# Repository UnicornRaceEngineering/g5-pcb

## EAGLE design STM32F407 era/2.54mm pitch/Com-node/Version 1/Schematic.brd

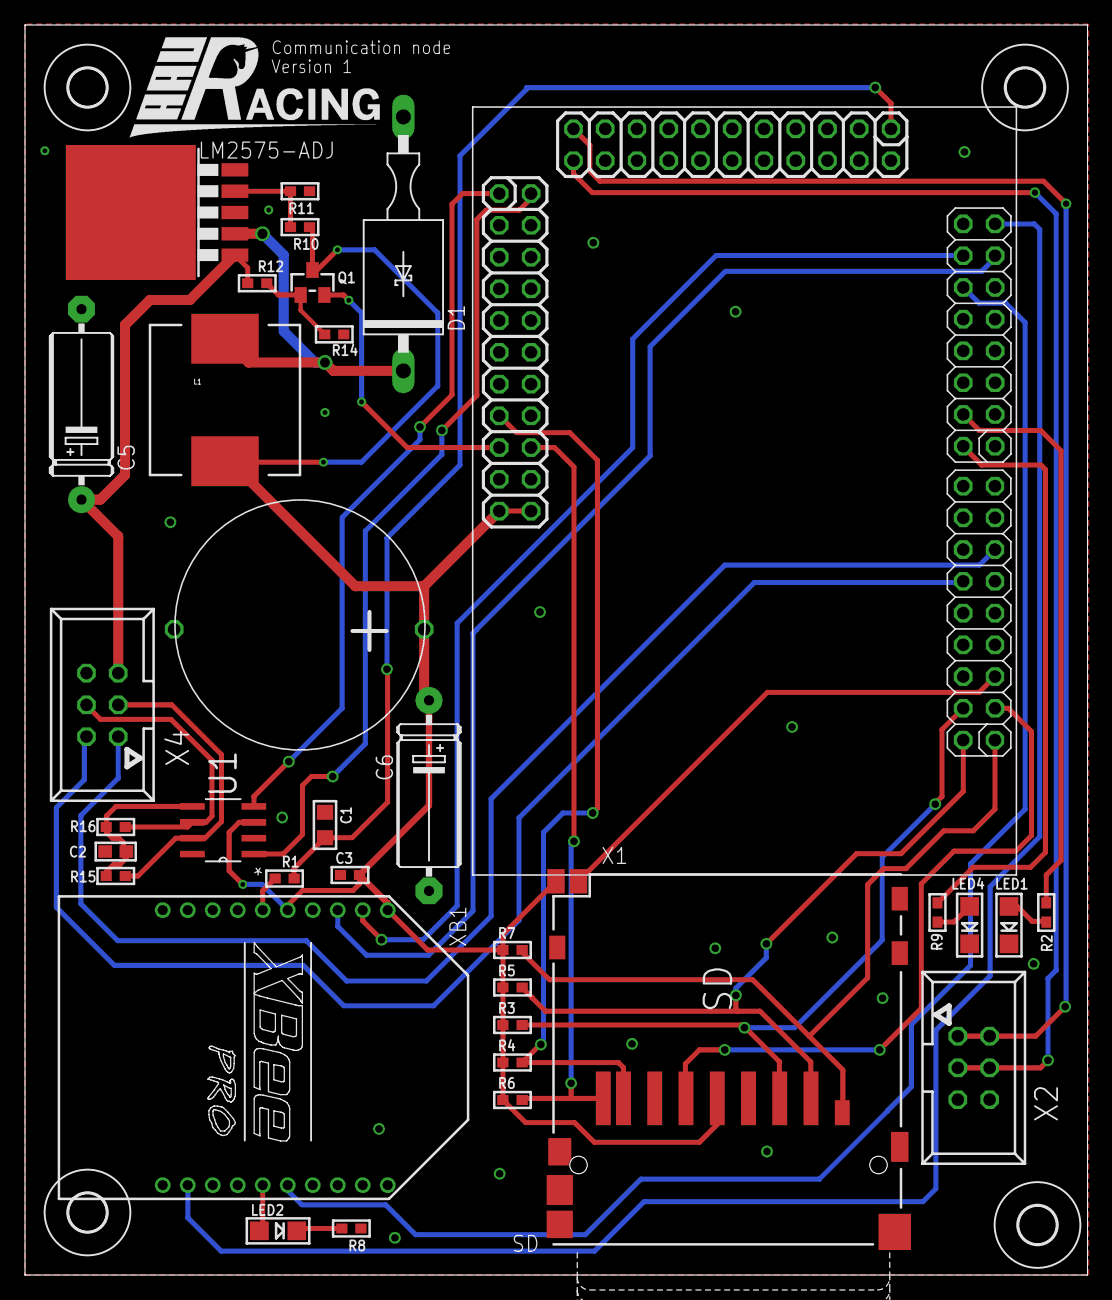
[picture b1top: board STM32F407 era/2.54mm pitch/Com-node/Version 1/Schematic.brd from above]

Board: 2 copper layers, 85.0 x 100.0 mm, 38 parts (0 on the bottom side), 35 nets.

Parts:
C1: 1µF; _0805
C2: 4n7; 0603
C3: 100nF; _0603
C5: 100uF; E15-5
C6: 220uF; E15-5
C8: SUPERCAP
D1: 1N5638; DO13M
H1, H2, H3, H4: MOUNT-HOLE3.0; 3,0
L1: 220µH; CDRH125
LED1, LED2, LED4: CHIPLED_1206
LM2575-ADJ: LM2596S; TO263-5
Q1: SOT23-WIDE
R1: 850; _0603
R2, R8, R9: 500; _0603
R3, R4, R5, R6, R7: 47k; _0603
R10: 1K69; _0603
R11: 1K; _0603
R12: 20K; _0603
R14: XXXXX; _0603
R15, R16: 60; _0603
U1: MAX13052ESA+; SOIC127P600X175-8N
U$1: CPU-BOARD; CPU-BOARD-JP1
X1: SDBMF; SDBMF-009XXBXX2
X2, X4: 057-006-1
XB1: XBEE-PRO

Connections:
+3V3: C3.2, C6.+, C8.P$1, L1.2, Q1.3, R3.1, R4.1, R5.1, R6.1, R7.1, R10.2, U1.3, U$1.P$43, U$1.P$44, X1.4, X1.SW3, XB1.1, XB1.5
+14V2: C5.+, LM2575-ADJ.1, R12.1, X4.5
CTS-XBEE: U$1.P$77, XB1.12
DEBUG-LED1: R9.2, U$1.P$64
DEBUG-LED2: R2.2, U$1.P$66
ECU_CAN_H: R15.2, U1.7, X4.3
ECU_CAN_L: R16.2, U1.6, X4.4
ECU_CAN_RX: U1.4, U$1.P$23
ECU_CAN_TX: U1.1, U$1.P$24
unnamed: R1.1, XB1.6
unnamed: LED1.A, R2.1
unnamed: LED2.A, XB1.15
unnamed: LED2.C, R8.2
unnamed: LED4.A, R9.1
unnamed: D1.C, L1.1, LM2575-ADJ.2
unnamed: LM2575-ADJ.4, R10.1, R11.2
unnamed: Q1.1, R12.2, R14.2
unnamed: C2.1, R15.1, R16.1, U1.5
PE: C1.1, C2.2, C3.1, C5.-, C6.-, C8.P$3, D1.A, LED1.C, LED4.C, LM2575-ADJ.3, LM2575-ADJ.5, R8.1, R11.1, R14.1, U1.2, U1.8, U$1.P$19, U$1.P$20, U$1.P$41, U$1.P$42, U$1.P$62, U$1.P$69, U$1.P$70, U$1.P$78, X1.3, X1.6, X2.5, X2.6, X4.6, XB1.10
RTS-XBEE: U$1.P$74, XB1.16
RX-XBEE: U$1.P$76, XB1.2
SDIO_CMD: R3.2, U$1.P$48, X1.2
SDIO_D0: R4.2, U$1.P$37, X1.7
SDIO_D1: R6.2, U$1.P$40, X1.8
SDIO_D2: R7.2, U$1.P$45, X1.9
SDIO_D3: R5.2, U$1.P$46, X1.1
SDIO_SCK: U$1.P$47, X1.5
SD_IN: U$1.P$49, X1.SW1
SS-XBEE: C1.2, R1.2, U$1.P$1
TX-XBEE: U$1.P$75, XB1.3
UART3_RX: U$1.P$22, X2.3, X2.4
UART3_TX: U$1.P$21, X2.1, X2.2
USART1_RX: U$1.P$57, X4.1
USART1_TX: U$1.P$56, X4.2
V-SENSE: Q1.2, U$1.P$39

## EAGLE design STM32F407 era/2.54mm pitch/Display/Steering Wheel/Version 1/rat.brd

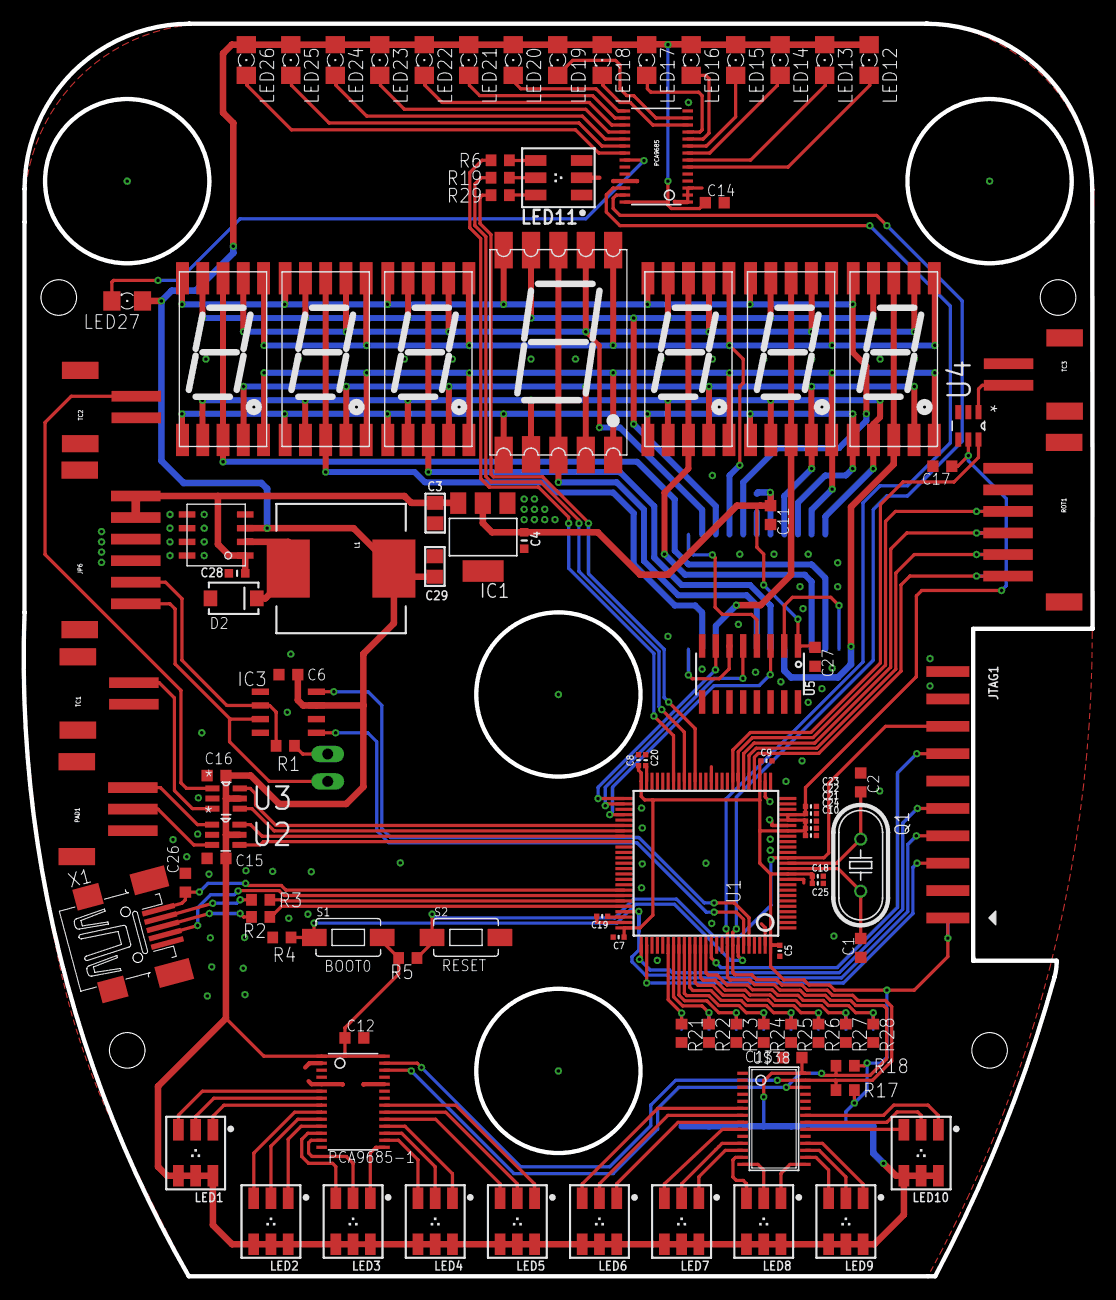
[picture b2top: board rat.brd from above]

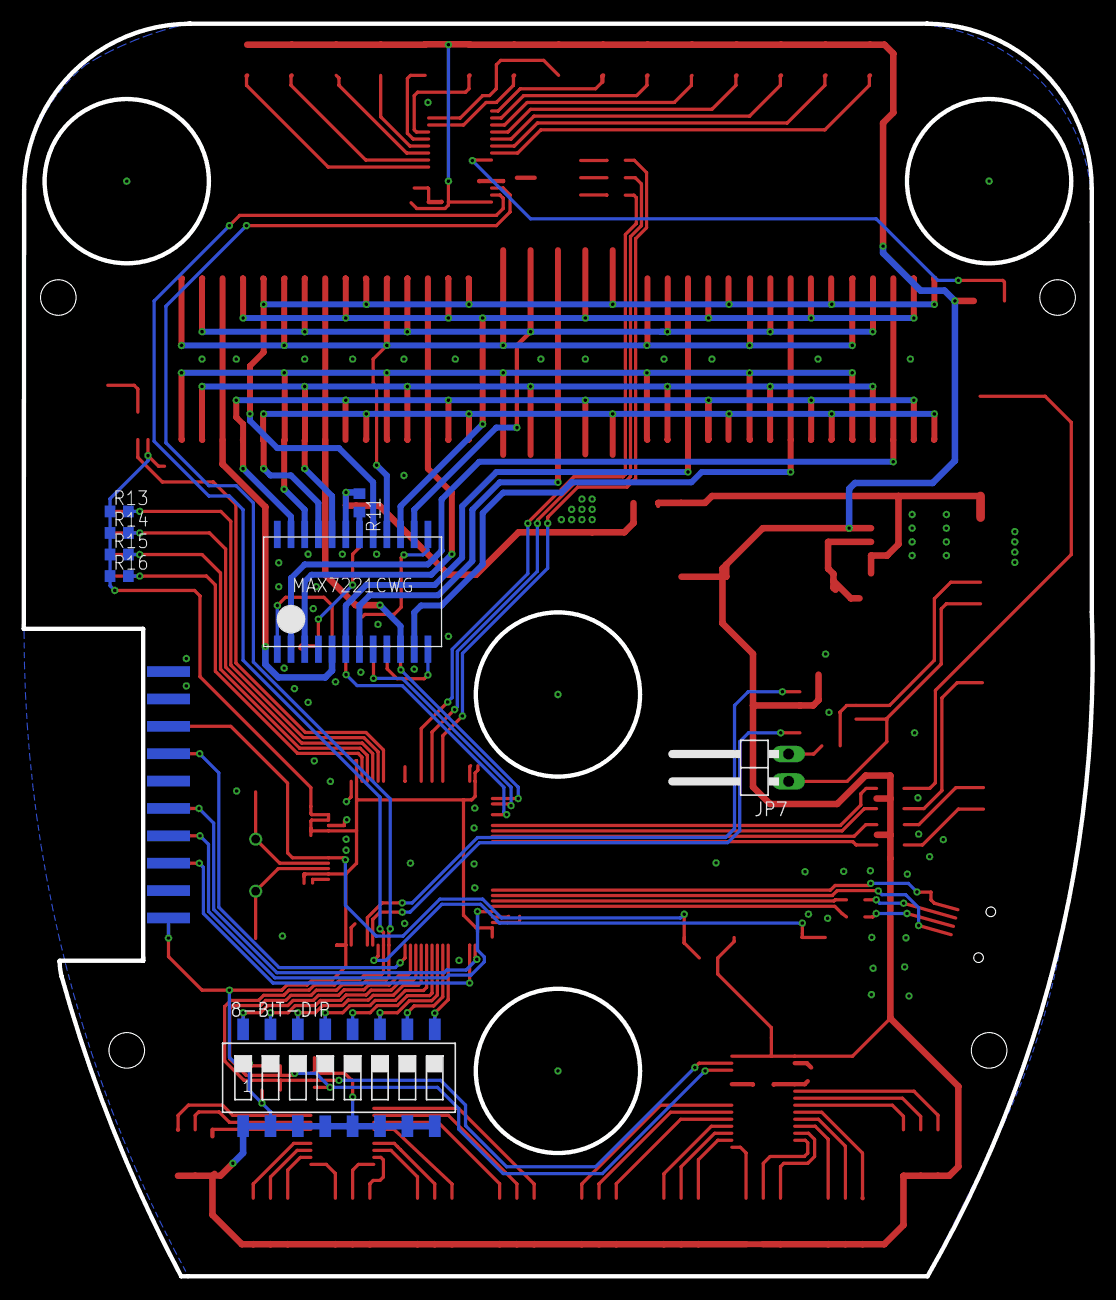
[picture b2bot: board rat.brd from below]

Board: 2 copper layers, 99.2 x 116.2 mm, 117 parts (8 on the bottom side), 124 nets.

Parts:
8-BIT-DIP: SWS008; SMS-008
C1, C2: 22pf; C0603K
C3, C29: 10u; 0805
C4: 22u; _0603MP
C5, C7, C8, C9, C10, C18, C21, C23: 100n; _0402MP
C6, C11, C12, C13, C14, C15, C16, C17, C27: 100nF; C0603K
C19, C20: 2u2; _0402MP
C22, C24: 1u; _0402MP
C25: 4u7; _0402MP
C26: 4u7; C0603K
C28: 100n; _0603MP
D2: B340A-13-F; SMA-DIODE
IC1: REG1117; SOT223
IC3: PCA82C250T; SO8
JP2, JP3, JP4, JP5: STAND-OFF
JP6: M06; S6B_PH
JP7: 1X02/90
JTAG1: JTAG-ARMEDGE; MOLEX20_RIGHTANGLE
L1: MSS1038-473MLC 47u; CDRH125
LED1, LED2, LED3, LED4, LED5, LED6, LED7, LED8, LED9, LED10, LED11: RGBLED_PLCC6
LED12, LED13, LED14, LED15, LED16: BLUE; 1206
LED17, LED18, LED19, LED20, LED21: RED; 1206
LED22, LED23, LED24, LED25, LED26, LED27: GREEN; 1206
MAX7221: MAX7221-SMD; MAX7221
PAD1: S3B-PH
PCA9685, PCA9685-1: TSSOP28
Q1: 25 MHz; HC49U70
R1: 120; R0603
R2, R3: 22; R0603
R4, R5: 500; R0603
R6, R19, R29: 220; R0603
R11: 9.5k; R0603
R13, R14, R15, R16, R17, R18: 10k; R0603
R21, R22, R23, R24, R25, R26, R27, R28: 200; R0603
ROT1: M06; S6B_PH
S1, S2: TACTILE-SWITCH-1101NE
TC1: NEUT; S2B-PH
TC2: LC; S2B-PH
TC3: tc; S2B-PH
U1: SQFP-S-14X14-100
U2, U3, U4: MAX6817EUT+T; SOT95P280X145-6N
U5: SOIC16
U$2, U$3, U$4, U$6, U$7, U$8: REDSEVENSEGMENT; REDSEGMENT
U$5: BIGSEVENSEGMENT
U$10: AP1509; SOP-8L
U$38: TLC59116; TSSOP28
X1: 32005-201

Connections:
3.3V: 8-BIT-DIP.1, 8-BIT-DIP.2, 8-BIT-DIP.3, 8-BIT-DIP.4, 8-BIT-DIP.5, 8-BIT-DIP.6, 8-BIT-DIP.7, 8-BIT-DIP.8, C5.1, C6.1, C7.1, C8.1, C9.1, C10.1, C12.1, C13.1, C14.1, C15.1, C16.1, C17.1, C18.1, C21.1, C22.1, C23.1, C24.1, C25.1, C29.1, IC3.3, JTAG1.1, JTAG1.2, L1.1, LED1.4, LED1.5, LED1.6, LED2.4, LED2.5, LED2.6, LED3.4, LED3.5, LED3.6, LED4.4, LED4.5, LED4.6, LED5.4, LED5.5, LED5.6, LED6.4, LED6.5, LED6.6, LED7.4, LED7.5, LED7.6, LED8.4, LED8.5, LED8.6, LED9.4, LED9.5, LED9.6, LED10.4, LED10.5, LED10.6, LED12.A, LED13.A, LED14.A, LED15.A, LED16.A, LED17.A, LED18.A, LED19.A, LED20.A, LED21.A, LED22.A, LED23.A, LED24.A, LED25.A, LED26.A, LED27.A, PCA9685.28, PCA9685-1.1, PCA9685-1.28, R5.2, R13.1, R14.1, R15.1, R16.1, R17.2, R18.2, S1.P$2, U1.11, U1.19, U1.21, U1.22, U1.28, U1.50, U1.75, U1.100, U2.5, U3.5, U4.5, U$10.P$3, U$38.28
5.0V: C4.1, C11.1, C27.1, IC1.2, MAX7221.VCC, R11.1, U5.1
12V: C3.2, C28.2, IC1.3, JP6.5, JP6.6, U$10.P$1
CANJUMP1: IC3.7, JP6.1, JP7.1
CANJUMP2: JP7.2, R1.2
CAN_RX: IC3.1, U1.95
CAN_TX: IC3.4, U1.96
DIP1: 8-BIT-DIP.9, R21.1, U1.81
DIP2: 8-BIT-DIP.10, R22.1, U1.82
DIP3: 8-BIT-DIP.11, R23.1, U1.83
DIP4: 8-BIT-DIP.12, R24.1, U1.84
DIP5: 8-BIT-DIP.13, R25.1, U1.85
DIP6: 8-BIT-DIP.14, R26.1, U1.86
DIP7: 8-BIT-DIP.15, R27.1, U1.87
DIP8: 8-BIT-DIP.16, R28.1, U1.88
GND: C1.1, C2.1, C3.1, C4.2, C5.2, C6.2, C7.2, C8.2, C9.2, C10.2, C11.2, C12.2, C13.2, C14.2, C15.2, C16.2, C17.2, C18.2, C19.2, C20.2, C21.2, C22.2, C23.2, C24.2, C25.2, C26.2, C27.2, C28.1, C29.2, D2.A, IC1.1, IC3.2, IC3.8, JP6.3, JP6.4, JTAG1.3, JTAG1.4, JTAG1.6, JTAG1.8, JTAG1.10, JTAG1.12, JTAG1.14, JTAG1.16, JTAG1.18, JTAG1.20, LED11.1, LED11.2, LED11.3, MAX7221.GND, MAX7221.GND1, PAD1.1, PCA9685.1, PCA9685.2, PCA9685.3, PCA9685.4, PCA9685.5, PCA9685.14, PCA9685.23, PCA9685.24, PCA9685.25, PCA9685-1.2, PCA9685-1.3, PCA9685-1.4, PCA9685-1.5, PCA9685-1.14, PCA9685-1.23, PCA9685-1.24, PCA9685-1.25, R4.1, R21.2, R22.2, R23.2, R24.2, R25.2, R26.2, R27.2, R28.2, ROT1.1, ROT1.2, S2.P$2, TC1.1, TC2.1, TC3.1, U1.10, U1.20, U1.27, U1.37, U1.74, U1.99, U2.2, U3.2, U4.2, U5.8, U$10.P$4, U$10.P$5, U$10.P$6, U$10.P$7, U$10.P$8, U$38.10, U$38.19, U$38.24, X1.5, X1.M1, X1.M2, X1.M3, X1.M4
JTAG-TCK: JTAG1.9, U1.76
JTAG-TDI: JTAG1.5, U1.77
JTAG-TDO: JTAG1.13, U1.89
JTAG-TMS: JTAG1.7, U1.72
LC: U1.56, U3.6
unnamed: C2.2, Q1.1, U1.13
unnamed: C1.2, Q1.2, U1.12
unnamed: MAX7221.SEG_A, U$2.A, U$3.A, U$4.A, U$5.A, U$6.A, U$7.A, U$8.A
unnamed: MAX7221.CLK, U5.4
unnamed: MAX7221.LOAD, U5.6
unnamed: MAX7221.SEG_B, U$2.B, U$3.B, U$4.B, U$5.B, U$6.B, U$7.B, U$8.B
unnamed: MAX7221.DIN, U5.2
unnamed: MAX7221.SEG_C, U$2.C, U$3.C, U$4.C, U$5.C, U$6.C, U$7.C, U$8.C
unnamed: LED13.C, PCA9685.7
unnamed: C19.1, U1.73
unnamed: LED14.C, PCA9685.8
unnamed: MAX7221.SEG_D, U$2.D, U$3.D, U$4.D, U$5.D, U$6.D, U$7.D, U$8.D
unnamed: MAX7221.SEG_E, U$2.E, U$3.E, U$4.E, U$5.E, U$6.E, U$7.E, U$8.E
unnamed: MAX7221.SEG_F, U$2.F, U$3.F, U$4.F, U$5.F, U$6.F, U$7.F, U$8.F
unnamed: MAX7221.SEG_G, U$2.G, U$3.G, U$4.G, U$5.G, U$6.G, U$7.G, U$8.G
unnamed: MAX7221.DIG0, U$2.GND, U$2.GND2
unnamed: MAX7221.DIG1, U$3.GND, U$3.GND2
unnamed: MAX7221.DIG2, U$4.GND, U$4.GND2
unnamed: MAX7221.DIG3, U$5.GND, U$5.GND2
unnamed: MAX7221.DIG4, U$6.GND, U$6.GND2
unnamed: MAX7221.DIG5, U$7.GND, U$7.GND2
unnamed: MAX7221.DIG6, U$8.GND, U$8.GND2
unnamed: LED15.C, PCA9685.9
unnamed: C20.1, U1.49
unnamed: MAX7221.SEG_DP, U$2.DP, U$3.DP, U$4.DP, U$5.DOT, U$6.DP, U$7.DP, U$8.DP
unnamed: R2.2, X1.3
unnamed: MAX7221.ISET, R11.2
unnamed: R3.2, X1.2
unnamed: LED11.5, R19.1
unnamed: R4.2, S1.P$1, U1.94
unnamed: LED11.6, R29.1
unnamed: LED11.4, R6.1
unnamed: LED16.C, PCA9685.10
unnamed: LED17.C, PCA9685.11
unnamed: LED18.C, PCA9685.12
unnamed: LED19.C, PCA9685.13
unnamed: LED20.C, PCA9685.15
unnamed: LED21.C, PCA9685.16
unnamed: LED22.C, PCA9685.17
unnamed: LED23.C, PCA9685.18
unnamed: LED24.C, PCA9685.19
unnamed: LED25.C, PCA9685.20
unnamed: LED26.C, PCA9685.21
unnamed: LED1.3, PCA9685-1.6
unnamed: D2.C, L1.2, U$10.P$2
unnamed: LED1.2, PCA9685-1.7
unnamed: LED1.1, PCA9685-1.8
unnamed: LED2.3, PCA9685-1.9
unnamed: IC3.6, JP6.2, R1.1
unnamed: LED2.2, PCA9685-1.10
unnamed: LED2.1, PCA9685-1.11
unnamed: LED3.3, PCA9685-1.12
unnamed: LED3.2, PCA9685-1.13
unnamed: LED3.1, PCA9685-1.15
unnamed: LED4.3, PCA9685-1.16
unnamed: LED12.C, PCA9685.6
unnamed: LED4.2, PCA9685-1.17
unnamed: LED4.1, PCA9685-1.18
unnamed: LED5.3, PCA9685-1.19
unnamed: LED5.2, PCA9685-1.20
unnamed: LED5.1, PCA9685-1.21
unnamed: LED6.3, U$38.6
unnamed: LED6.2, U$38.7
unnamed: LED6.1, U$38.8
unnamed: LED7.3, U$38.9
unnamed: LED7.2, U$38.11
unnamed: LED7.1, U$38.12
unnamed: LED8.3, U$38.13
unnamed: LED8.2, U$38.14
unnamed: LED8.1, U$38.15
unnamed: LED9.3, U$38.16
unnamed: LED9.2, U$38.17
unnamed: LED9.1, U$38.18
unnamed: LED10.3, U$38.20
unnamed: LED10.2, U$38.21
unnamed: LED10.1, U$38.22
unnamed: LED27.C, PCA9685.22
unnamed: TC1.2, U3.3
unnamed: PAD1.3, U2.1
unnamed: PAD1.2, U2.3
unnamed: TC2.2, U3.1
unnamed: TC3.2, U4.1
NEUT: U1.57, U3.4
PADDOWN: U1.59, U2.4
PADUP: U1.58, U2.6
RESET: JTAG1.15, R5.1, S2.P$1, U1.14
ROTSW1: R16.2, ROT1.6, U1.29
ROTSW2: R15.2, ROT1.5, U1.30
ROTSW3: R14.2, ROT1.4, U1.31
ROTSW4: R13.2, ROT1.3, U1.32
SCL: PCA9685.26, PCA9685-1.26, R18.1, U1.92, U$38.26
SDA: PCA9685.27, PCA9685-1.27, R17.1, U1.93, U$38.27
SLBLUE: R29.2, U1.40
SLGREEN: R19.2, U1.42
SLRED: R6.2, U1.44
SPI-LOAD: U1.51, U5.7
SPI-MOSI: U1.54, U5.3
SPI-SCK: U1.52, U5.5
TCTEMPOFF: U1.33, U4.6
USB_DM: R3.1, U1.70
USB_DP: R2.1, U1.71
USB_ID: U1.69, X1.4
USB_VBUS: C26.1, U1.68, X1.1

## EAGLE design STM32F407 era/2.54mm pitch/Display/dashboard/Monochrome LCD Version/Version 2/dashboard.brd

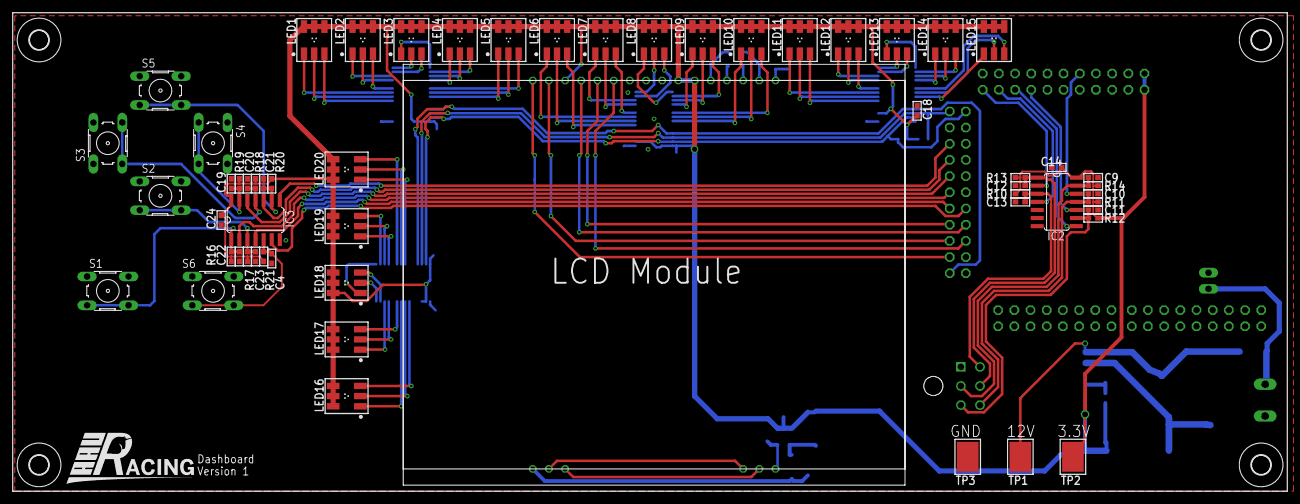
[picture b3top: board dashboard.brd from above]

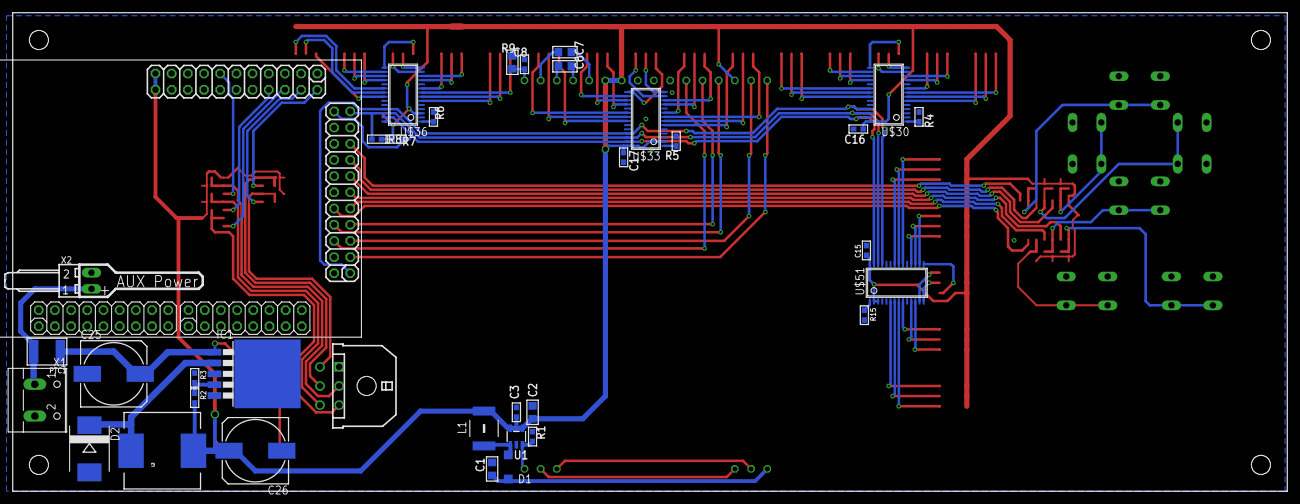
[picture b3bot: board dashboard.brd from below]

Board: 2 copper layers, 200.0 x 75.1 mm, 97 parts (36 on the bottom side), 110 nets.

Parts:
C1: 220n; _0805
C2: 1u; _0805
C3, C4, C8, C9, C10, C11, C12, C13, C14, C15, C16, C17, C18, C19, C20, C21, C22, C23, C24: 100n; _0603
C6, C7: 2u; _0805
C25: 470u; 153CLV-1012
C26: 220u; 153CLV-1012
D1: MBR0520LT; SOD123
D2: SMC
H1, H2, H3, H4: MOUNT-HOLE3.0; 3,0
IC1: TO263-5
IC2, IC3: 74HC14D; SO14
L1: WE-PD4S; S
L2: MSS1583-683MED; CDRH125
LED1, LED2, LED3, LED4, LED5, LED6, LED7, LED8, LED9, LED10, LED11, LED12, LED13, LED14, LED15, LED16, LED17, LED18, LED19, LED20: RGBLED_PLCC6
PTC1: PTC1812
R1: 15; _0603
R2: 1k69; _0603
R3: 1k; _0603
R4, R5, R6, R15: 931; _0603
R7, R8, R10, R11, R12, R13, R14, R16, R17, R18, R19, R20, R21: 500; _0603
R9: 10m; _0805
S1, S2, S3, S4, S5, S6: B3F-10XX
TP1, TP2, TP3: TESTPOINT_SMT
U1: CAT4238TD-GT3; SOT23-5
U$1: CPU-BOARD; CPU-BOARD-JP1
U$10: EA-DOGXL160W-7
U$30, U$33, U$36, U$51: TLC59116; TSSOP28
U$42: MICROFIT6; 43045-0600
X1: W237-102
X2: 22-05-7028-02; 7395-02

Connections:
3.3V: C2.1, C3.1, C14.1, C15.1, C16.1, C17.1, C18.1, C24.1, C26.+, IC2.14, IC3.14, L1.2, L2.2, LED1.4, LED1.5, LED1.6, LED2.4, LED2.5, LED2.6, LED3.4, LED3.5, LED3.6, LED4.4, LED4.5, LED4.6, LED5.4, LED5.5, LED5.6, LED6.4, LED6.5, LED6.6, LED7.4, LED7.5, LED7.6, LED8.4, LED8.5, LED8.6, LED9.4, LED9.5, LED9.6, LED10.4, LED10.5, LED10.6, LED11.4, LED11.5, LED11.6, LED12.4, LED12.5, LED12.6, LED13.4, LED13.5, LED13.6, LED14.4, LED14.5, LED14.6, LED15.4, LED15.5, LED15.6, LED16.4, LED16.5, LED16.6, LED17.4, LED17.5, LED17.6, LED18.4, LED18.5, LED18.6, LED19.4, LED19.5, LED19.6, LED20.4, LED20.5, LED20.6, R2.2, R7.2, R8.2, R10.2, R11.2, R12.2, R13.2, R14.2, R16.2, R17.2, R18.2, R19.2, R20.2, R21.2, TP2.P$1, U1.4, U1.5, U$1.P$43, U$1.P$44, U$10.P$22, U$10.P$23, U$10.P$30, U$30.28, U$33.2, U$33.28, U$36.3, U$36.28, U$51.2, U$51.3, U$51.28
12V: PTC1.P$2, X1.1, X2.1
BTN1: C12.2, IC2.1, R13.1, U$42.P$5
BTN1S: IC2.2, U$1.P$24
BTN2: C13.2, IC2.3, R10.1, U$42.P$4
BTN2S: IC2.4, U$1.P$26
BTN3: C10.2, IC2.11, R11.1, U$42.P$6
BTN3S: IC2.10, U$1.P$30
BTN4: C9.2, IC2.13, R14.1, U$42.P$2
BTN4S: IC2.12, U$1.P$35
BTN5: C11.2, IC2.9, R12.1, U$42.P$3
BTN5S: IC2.8, U$1.P$28
CD: U$1.P$6, U$10.P$27
GND: C1.2, C2.2, C3.2, C4.1, C8.1, C9.1, C10.1, C11.1, C12.1, C13.1, C14.2, C15.2, C16.2, C17.2, C18.2, C19.1, C20.1, C21.1, C22.1, C23.1, C24.2, C25.-, C26.-, D2.A, IC1.3, IC1.5, IC1.6, IC2.5, IC2.7, IC3.7, R1.2, R3.1, R4.2, R5.2, R6.2, R9.1, R15.2, S1.1, S1.2, S2.1, S2.2, S3.1, S3.2, S4.1, S4.2, S5.1, S5.2, S6.1, S6.2, TP3.P$1, U1.2, U$1.P$19, U$1.P$20, U$1.P$41, U$1.P$42, U$1.P$62, U$1.P$69, U$1.P$70, U$1.P$78, U$10.P$24, U$10.P$25, U$10.P$26, U$30.2, U$30.3, U$30.4, U$30.5, U$30.10, U$30.19, U$30.24, U$33.3, U$33.4, U$33.5, U$33.10, U$33.19, U$33.24, U$36.2, U$36.4, U$36.5, U$36.10, U$36.19, U$36.24, U$42.P$1, U$51.4, U$51.5, U$51.10, U$51.19, U$51.24, X1.2, X2.2
LCD_CLOCK: U$1.P$3, U$10.P$32
LCD_CS: U$1.P$7, U$10.P$28
LCD_DATA: U$1.P$5, U$10.P$31
LCD_RESET: U$1.P$8, U$10.P$29
unnamed: U$10.P$2, U$10.P$14
unnamed: U$10.P$3, U$10.P$15
unnamed: R1.1, U1.3, U$10.P$16
unnamed: C1.1, D1.C, U$10.P$1
unnamed: D1.A, L1.1, U1.1
unnamed: D2.C, IC1.2, L2.1
unnamed: LED1.3, U$30.6
unnamed: LED1.2, U$30.7
unnamed: IC1.4, R2.1, R3.2
unnamed: LED1.1, U$30.8
unnamed: LED2.3, U$30.9
unnamed: LED2.2, U$30.11
unnamed: LED2.1, U$30.12
unnamed: LED3.3, U$30.13
unnamed: LED3.2, U$30.14
unnamed: LED3.1, U$30.15
unnamed: LED4.3, U$30.16
unnamed: LED4.2, U$30.17
unnamed: LED4.1, U$30.18
unnamed: LED5.3, U$30.20
unnamed: LED5.2, U$30.21
unnamed: LED5.1, U$30.22
unnamed: LED6.3, U$33.6
unnamed: LED6.2, U$33.7
unnamed: LED6.1, U$33.8
unnamed: LED7.3, U$33.9
unnamed: LED7.2, U$33.11
unnamed: LED7.1, U$33.12
unnamed: LED8.3, U$33.13
unnamed: LED8.2, U$33.14
unnamed: LED8.1, U$33.15
unnamed: LED9.3, U$33.16
unnamed: LED9.2, U$33.17
unnamed: LED9.1, U$33.18
unnamed: LED10.3, U$33.20
unnamed: LED10.2, U$33.21
unnamed: LED10.1, U$33.22
unnamed: LED11.3, U$36.6
unnamed: LED11.2, U$36.7
unnamed: LED11.1, U$36.8
unnamed: LED12.3, U$36.9
unnamed: LED12.2, U$36.11
unnamed: LED12.1, U$36.12
unnamed: LED13.3, U$36.13
unnamed: LED13.2, U$36.14
unnamed: LED13.1, U$36.15
unnamed: LED14.3, U$36.16
unnamed: LED14.2, U$36.17
unnamed: LED14.1, U$36.18
unnamed: LED15.3, U$36.20
unnamed: LED15.2, U$36.21
unnamed: LED15.1, U$36.22
unnamed: R4.1, U$30.1
unnamed: LED16.3, U$51.6
unnamed: R5.1, U$33.1
unnamed: R6.1, U$36.1
unnamed: C6.1, U$10.P$20
unnamed: C7.1, U$10.P$21
unnamed: C6.2, U$10.P$19
unnamed: C7.2, U$10.P$18
unnamed: C8.2, R9.2, U$10.P$17
unnamed: LED16.2, U$51.7
unnamed: LED16.1, U$51.8
unnamed: LED17.3, U$51.9
unnamed: LED17.2, U$51.11
unnamed: LED17.1, U$51.12
unnamed: LED18.3, U$51.13
unnamed: LED18.2, U$51.14
unnamed: LED18.1, U$51.15
unnamed: LED19.3, U$51.16
unnamed: LED19.2, U$51.17
unnamed: LED19.1, U$51.18
unnamed: LED20.3, U$51.20
unnamed: LED20.2, U$51.21
unnamed: LED20.1, U$51.22
unnamed: R15.1, U$51.1
SCL: R8.1, U$1.P$21, U$30.26, U$33.26, U$36.26, U$51.26
SDA: R7.1, U$1.P$22, U$30.27, U$33.27, U$36.27, U$51.27
SW1: C22.2, IC3.1, R16.1, S1.3, S1.4
SW1S: IC3.2, U$1.P$11
SW2: C23.2, IC3.3, R17.1, S2.3, S2.4
SW2S: IC3.4, U$1.P$9
SW3: C20.2, IC3.11, R18.1, S3.3, S3.4
SW3S: IC3.10, U$1.P$15
SW4: C19.2, IC3.13, R19.1, S4.3, S4.4
SW4S: IC3.12, U$1.P$13
SW5: C21.2, IC3.9, R20.1, S5.3, S5.4
SW5S: IC3.8, U$1.P$17
SW6: C4.2, IC3.5, R21.1, S6.3, S6.4
SW6S: IC3.6, U$1.P$10
VSUP: C25.+, IC1.1, PTC1.P$1, TP1.P$1
~RESET: U$1.P$1, U$30.25, U$33.25, U$36.25, U$51.25

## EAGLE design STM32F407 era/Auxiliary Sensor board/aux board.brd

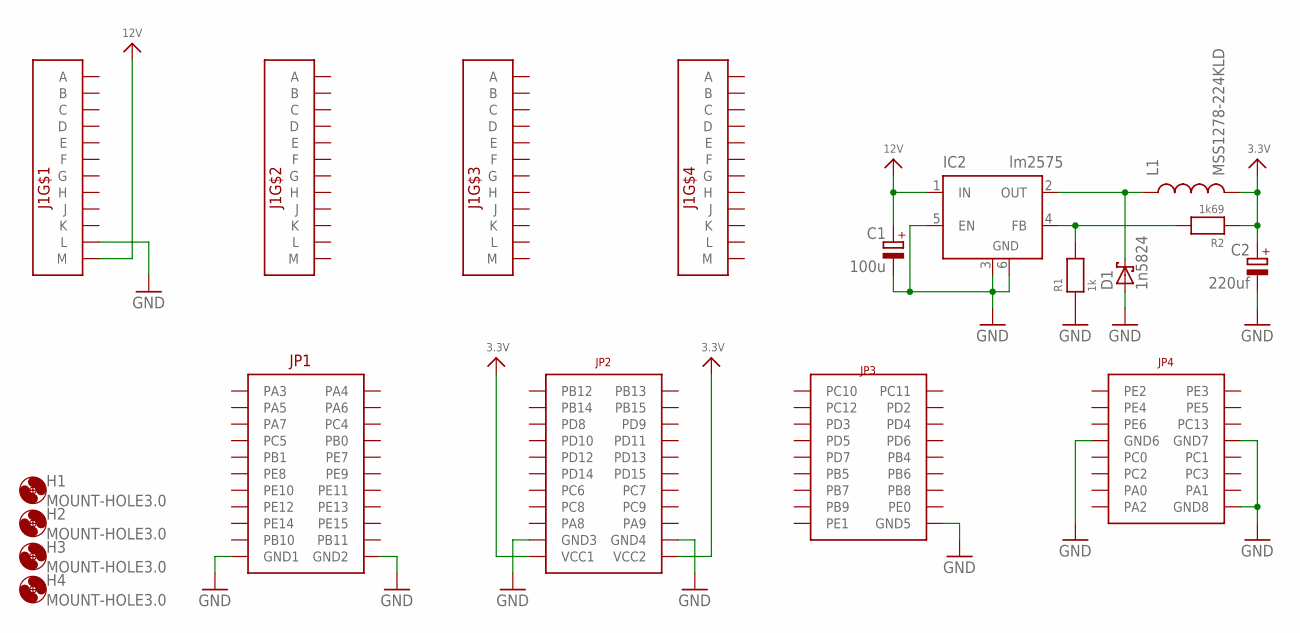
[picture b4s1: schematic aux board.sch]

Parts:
C1: 100u; E2,5-7
C2: 220uf; E3,5-8
D1: 1n5824; F126Z12
H1, H2, H3, H4: MOUNT-HOLE3.0; 3,0
IC2: lm2575; TO263-5
J1: AUTOCONNECTOR
L1: MSS1278-224KLD; CDRH125
R1: 1k; _0603
R2: 1k69; _0603
U$1: CPU-BOARD; CPU-BOARD-JP1

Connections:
3.3V: C2.+, L1.2, R2.1, U$1.P$43 (VCC1), U$1.P$44 (VCC2)
12V: C1.+, IC2.1 (IN), J1.M1 (M)
GND: C1.-, C2.-, D1.A, IC2.3 (GND), IC2.5 (EN), IC2.6 (GND), J1.L1 (L), R1.1, U$1.P$21 (GND1), U$1.P$22 (GND2), U$1.P$41 (GND3), U$1.P$42 (GND4), U$1.P$62 (GND5), U$1.P$69 (GND6), U$1.P$70 (GND7), U$1.P$78 (GND8)
unnamed: IC2.4 (FB), R1.2, R2.2
unnamed: D1.C, IC2.2 (OUT), L1.1

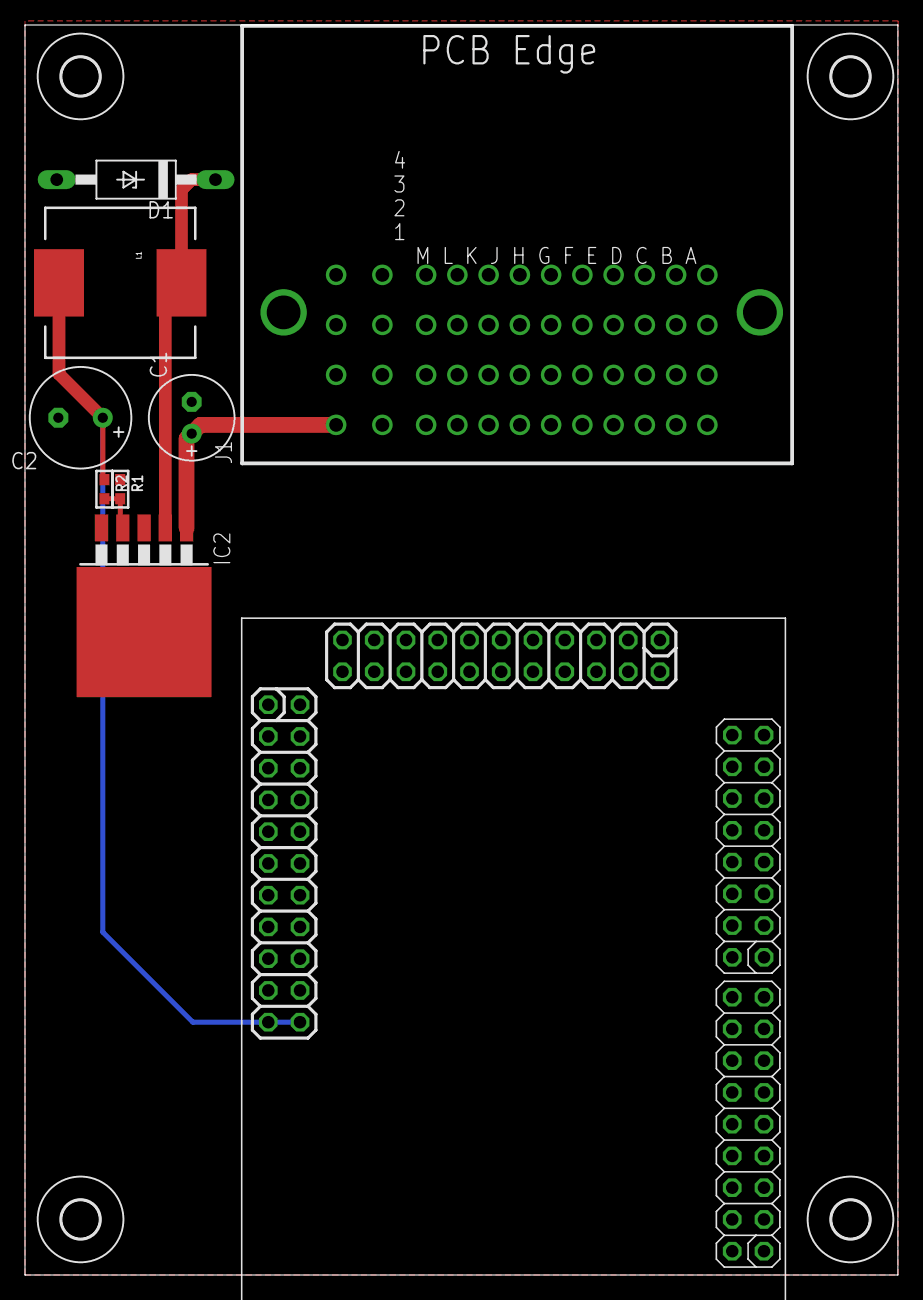
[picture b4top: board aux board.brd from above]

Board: 2 copper layers, 69.8 x 100.0 mm, 13 parts (0 on the bottom side), 5 nets.

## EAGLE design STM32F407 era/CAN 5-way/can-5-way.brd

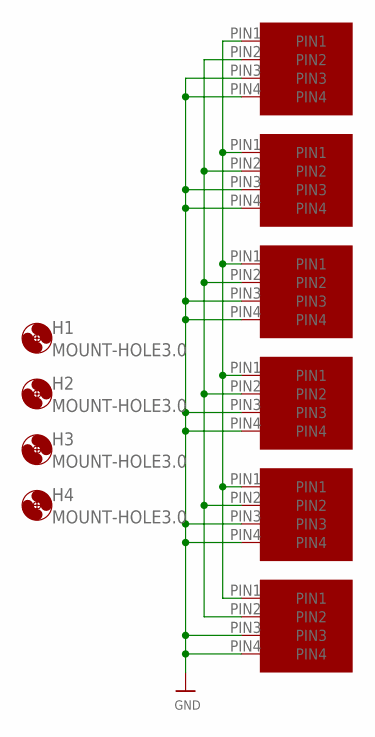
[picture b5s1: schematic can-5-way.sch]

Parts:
H1, H2, H3, H4: MOUNT-HOLE3.0; 3,0
U$1, U$2, U$3, U$4, U$5, U$7: MICROFIT4; MICROFIT4SOCK

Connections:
GND: U$1.PIN3, U$1.PIN4, U$2.PIN3, U$2.PIN4, U$3.PIN3, U$3.PIN4, U$4.PIN3, U$4.PIN4, U$5.PIN3, U$5.PIN4, U$7.PIN3, U$7.PIN4
unnamed: U$1.PIN1, U$2.PIN1, U$3.PIN1, U$4.PIN1, U$5.PIN1, U$7.PIN1
unnamed: U$1.PIN2, U$2.PIN2, U$3.PIN2, U$4.PIN2, U$5.PIN2, U$7.PIN2

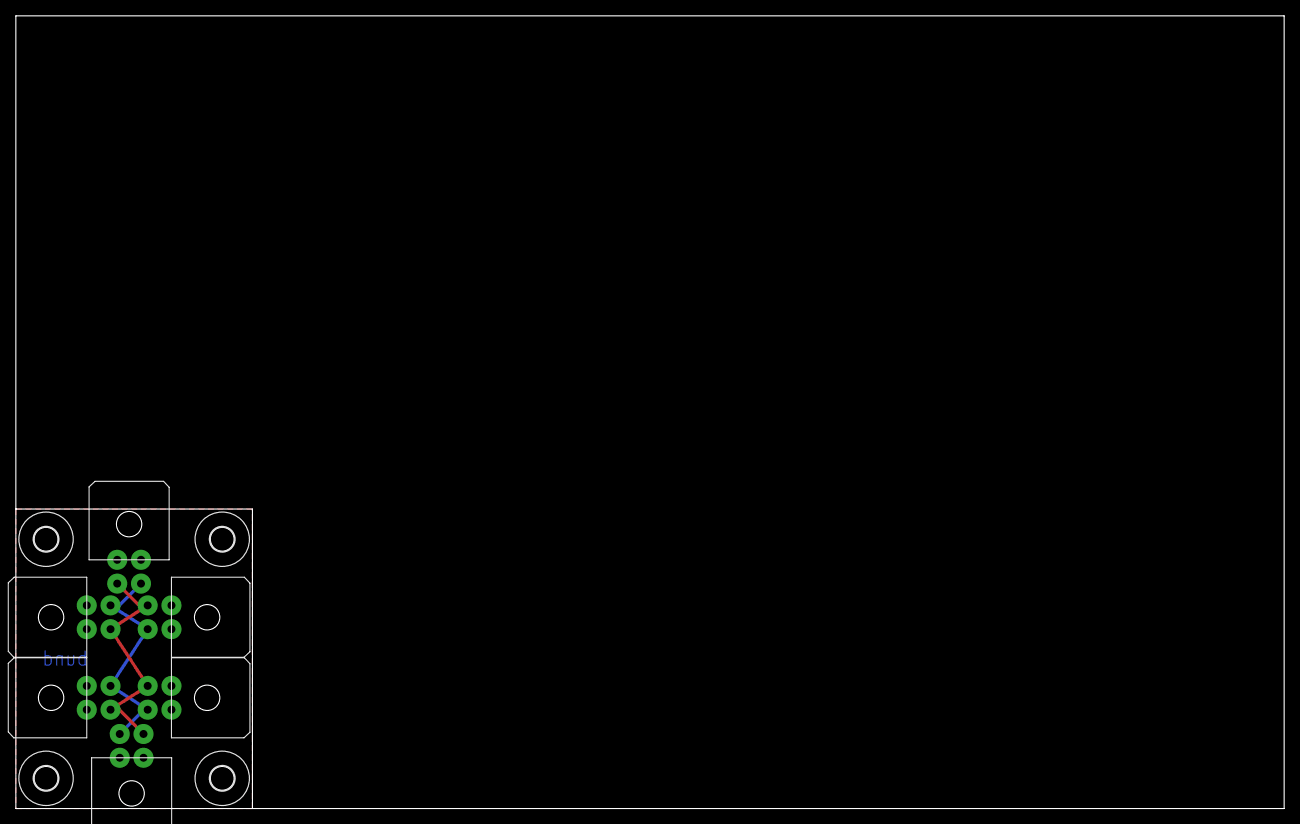
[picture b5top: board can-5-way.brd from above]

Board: 2 copper layers, 160.0 x 100.0 mm, 10 parts (0 on the bottom side), 3 nets.

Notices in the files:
parts and their libraries:
SparkFun-Passives: Licensing: Creative Commons ShareAlike 4.0 International - https://creativecommons.org/licenses/by-sa/4.0
microbuilder: This work is placed in the public domain, and may be freely used for commercial and non-commercial work with the following conditions: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
